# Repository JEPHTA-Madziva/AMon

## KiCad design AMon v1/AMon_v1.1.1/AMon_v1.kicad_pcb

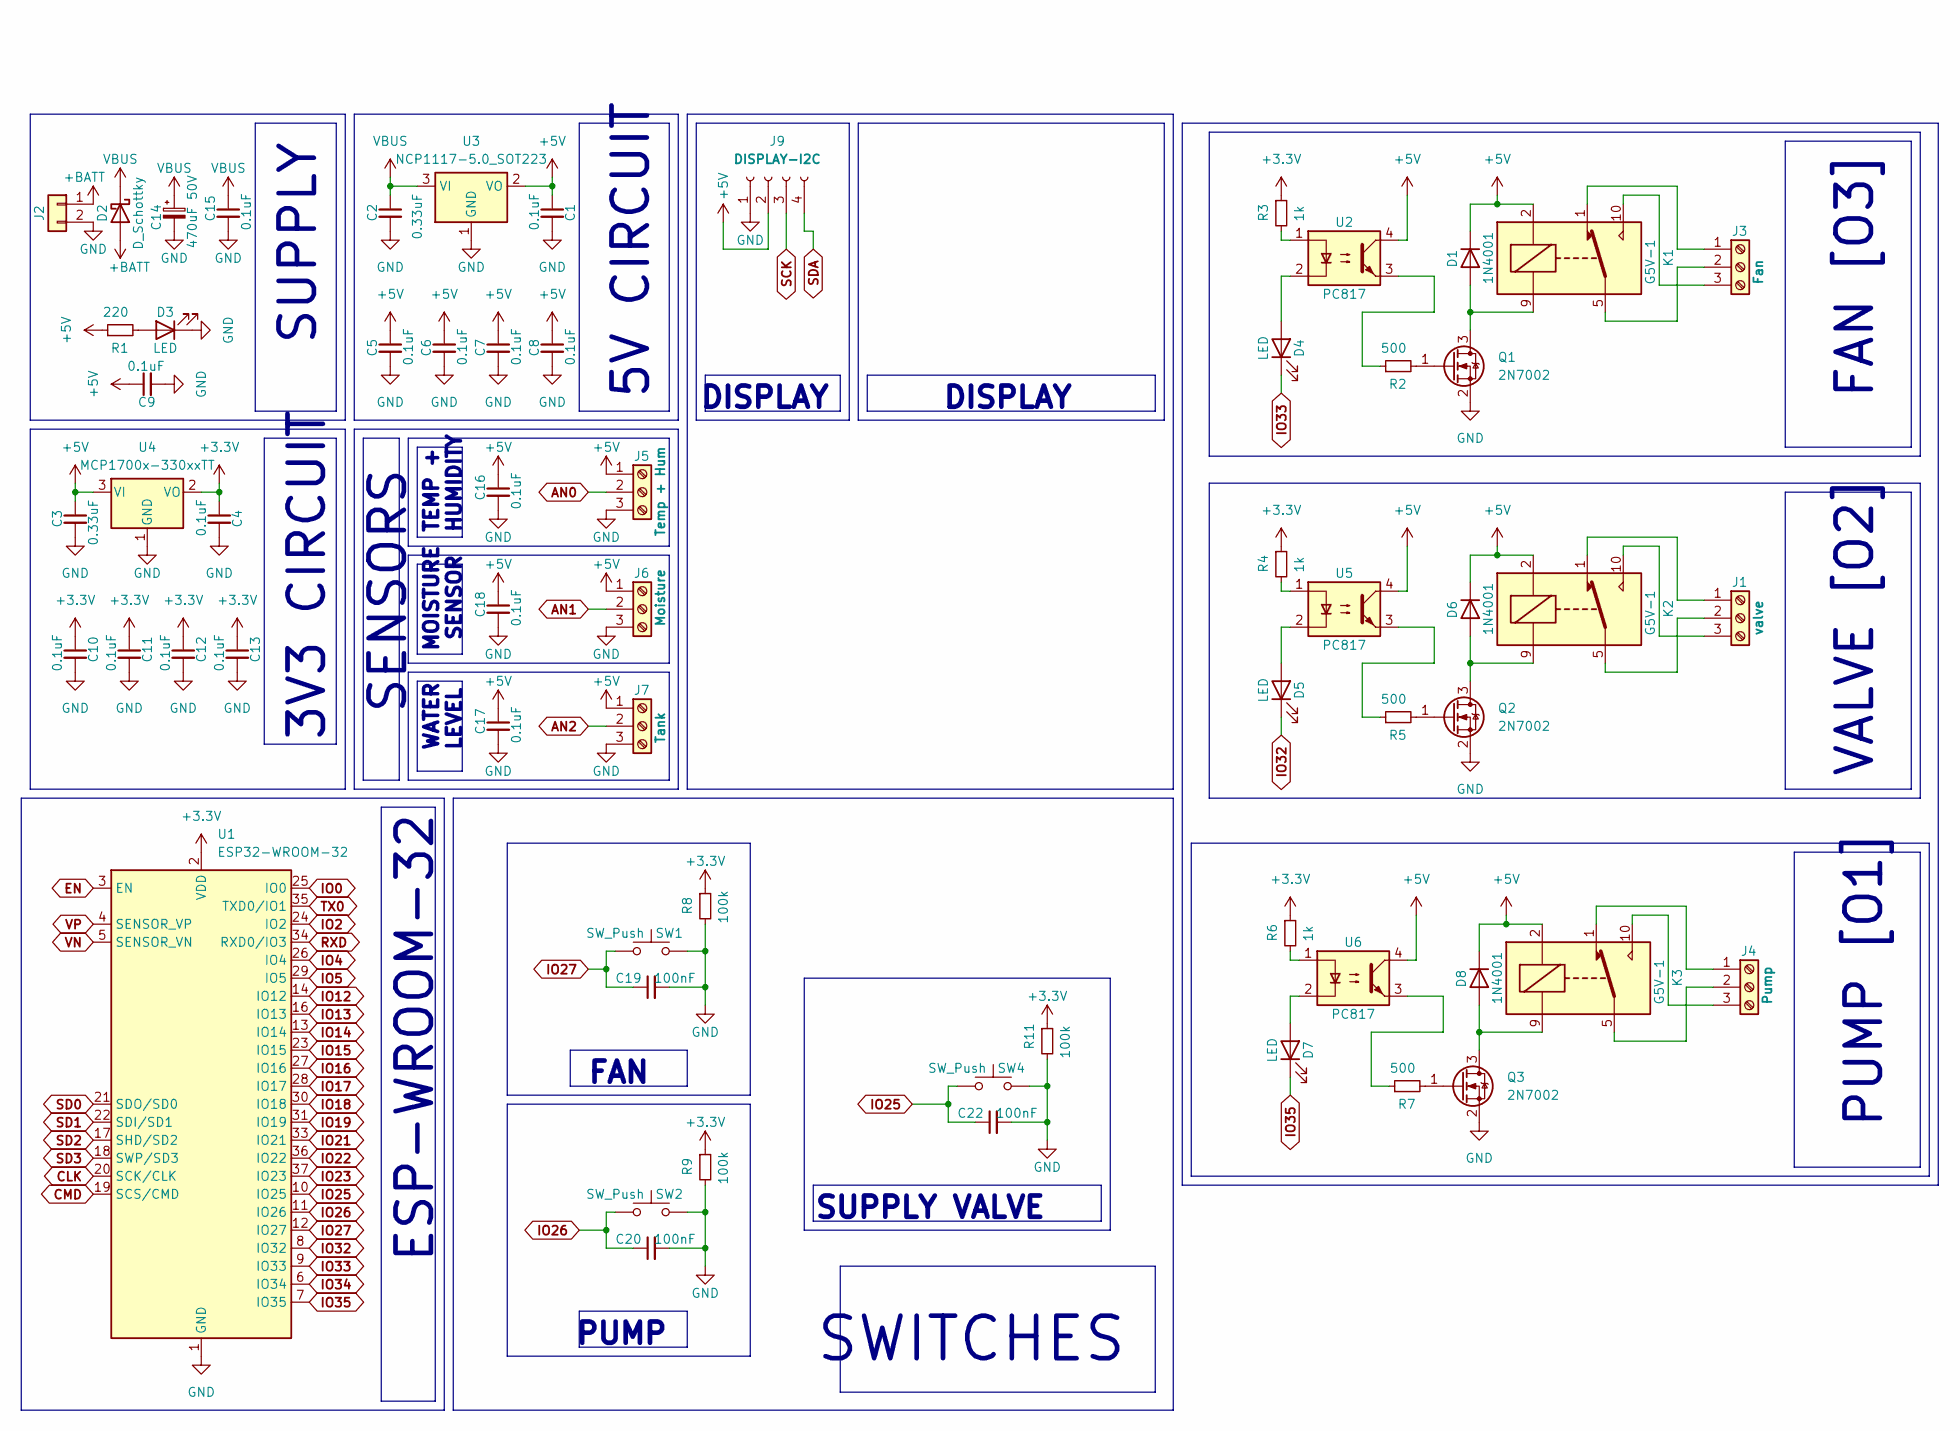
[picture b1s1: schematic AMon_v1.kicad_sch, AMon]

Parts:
C1, C4, C5, C6, C7, C8, C9, C10, C11, C12, C13, C15, C16, C17, C18: 0.1uF; C_1206_3216Metric
C2, C3: 0.33uF; C_1206_3216Metric
C14: 470uF 50V; CP_Elec_5x3.9
C19, C20, C22: 100nF; C_1206_3216Metric
D1, D6, D8: 1N4001; D_DO-41_SOD81_P10.16mm_Horizontal
D2: D_Schottky; D_DO-35_SOD27_P7.62mm_Horizontal
D3, D4, D5, D7: LED; LED_0805_2012Metric
J1: valve; TerminalBlock_Phoenix_MKDS-3-3-5.08_1x03_P5.08mm_Horizontal
J2: Conn_01x02; JST_EH_S2B-EH_1x02_P2.50mm_Horizontal
J3: Fan; TerminalBlock_Phoenix_MKDS-3-3-5.08_1x03_P5.08mm_Horizontal
J4: Pump; TerminalBlock_Phoenix_MKDS-3-3-5.08_1x03_P5.08mm_Horizontal
J5: Temp + Hum; TerminalBlock_Phoenix_MKDS-3-3-5.08_1x03_P5.08mm_Horizontal
J6: Moisture; TerminalBlock_Phoenix_MKDS-3-3-5.08_1x03_P5.08mm_Horizontal
J7: Tank; TerminalBlock_Phoenix_MKDS-3-3-5.08_1x03_P5.08mm_Horizontal
J9: DISPLAY-I2C; PinSocket_1x04_P2.54mm_Vertical
K1, K2, K3: G5V-1; Relay_SPDT_Omron_G5V-1
Q1, Q2, Q3: 2N7002; SOT-23
R1: 220; R_1206_3216Metric
R2, R5, R7: 500; R_1206_3216Metric
R3, R4, R6: 1k; R_1206_3216Metric
R8, R9, R11: 100k; R_1206_3216Metric
SW1, SW2, SW4: SW_Push; SW_SPST_B3U-1000P
U1: ESP32-WROOM-32
U2, U5, U6: PC817; DIP-4_W7.62mm
U3: NCP1117-5.0_SOT223; SOT-223-3_TabPin2
U4: MCP1700x-330xxTT; SOT-23

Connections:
+3.3V: C4.1, C10.1, C11.1, C12.1, C13.1, R3.1, R4.1, R6.1, R8.1, R9.1, R11.1, U1.2 (VDD), U4.2 (VO)
+5V: C1.1, C3.1, C5.1, C6.1, C7.1, C8.1, C9.1, C16.1, C17.1, C18.1, D1.1 (K), D6.1 (K), D8.1 (K), J5.1, J6.1, J7.1, J9.2, K1.2, K2.2, K3.2, R1.1, U2.4, U3.2 (VO), U4.3 (VI), U5.4, U6.4
+BATT: D2.2 (A), J2.1
AN0: J5.2
AN1: J6.2
AN2: J7.2
CLK: U1.20 (SCK/CLK)
CMD: U1.19 (SCS/CMD)
EN: U1.3 (EN)
GND: C1.2, C2.2, C3.2, C4.2, C5.2, C6.2, C7.2, C8.2, C9.2, C10.2, C11.2, C12.2, C13.2, C14.2, C15.2, C16.2, C17.2, C18.2, C19.2, C20.2, C22.2, D3.1 (K), J2.2, J5.3, J6.3, J7.3, J9.1, Q1.2 (S), Q2.2 (S), Q3.2 (S), R8.2, R9.2, R11.2, SW1.2, SW2.2, SW4.2, U1.1 (GND), U1.15 (GND), U1.38 (GND), U1.39 (GND), U3.1 (GND), U4.1 (GND)
IO0: U1.25 (IO0)
IO2: U1.24 (IO2)
IO4: U1.26 (IO4)
IO5: U1.29 (IO5)
IO12: U1.14 (IO12)
IO13: U1.16 (IO13)
IO14: U1.13 (IO14)
IO15: U1.23 (IO15)
IO16: U1.27 (IO16)
IO17: U1.28 (IO17)
IO18: U1.30 (IO18)
IO19: U1.31 (IO19)
IO21: U1.33 (IO21)
IO22: U1.36 (IO22)
IO23: U1.37 (IO23)
IO25: C22.1, SW4.1, U1.10 (IO25)
IO26: C20.1, SW2.1, U1.11 (IO26)
IO27: C19.1, SW1.1, U1.12 (IO27)
IO32: D5.1 (K), U1.8 (IO32)
IO33: D4.1 (K), U1.9 (IO33)
IO34: U1.6 (IO34)
IO35: D7.1 (K), U1.7 (IO35)
unnamed: D1.2 (A), K1.9, Q1.3 (D)
unnamed: D3.2 (A), R1.2
unnamed: D4.2 (A), U2.2
unnamed: D5.2 (A), U5.2
unnamed: D6.2 (A), K2.9, Q2.3 (D)
unnamed: D7.2 (A), U6.2
unnamed: D8.2 (A), K3.9, Q3.3 (D)
unnamed: J1.1, K2.1
unnamed: J1.2, K2.5, K2.6
unnamed: J1.3, K2.10
unnamed: J3.1, K1.1
unnamed: J3.2, K1.5, K1.6
unnamed: J3.3, K1.10
unnamed: J4.1, K3.1
unnamed: J4.2, K3.5, K3.6
unnamed: J4.3, K3.10
unnamed: Q1.1 (G), R2.2
unnamed: Q2.1 (G), R5.2
unnamed: Q3.1 (G), R7.2
unnamed: R2.1, U2.3
unnamed: R3.2, U2.1
unnamed: R4.2, U5.1
unnamed: R5.1, U5.3
unnamed: R6.2, U6.1
unnamed: R7.1, U6.3
RXD: U1.34 (RXD0/IO3)
SCK: J9.3
SD0: U1.21 (SDO/SD0)
SD1: U1.22 (SDI/SD1)
SD2: U1.17 (SHD/SD2)
SD3: U1.18 (SWP/SD3)
SDA: J9.4
TX0: U1.35 (TXD0/IO1)
VBUS: C2.1, C14.1, C15.1, D2.1 (K), U3.3 (VI)
VN: U1.5 (SENSOR_VN)
VP: U1.4 (SENSOR_VP)

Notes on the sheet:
TEMP + HUMIDITY
MOISTURE SENSOR
FAN
SUPPLY VALVE
ESP-WROOM-32
DISPLAY
WATER LEVEL
PUMP [O1]
VALVE [O2]
3V3 CIRCUIT
5V CIRCUIT
PUMP
FAN [O3]
SUPPLY
SENSORS
SWITCHES

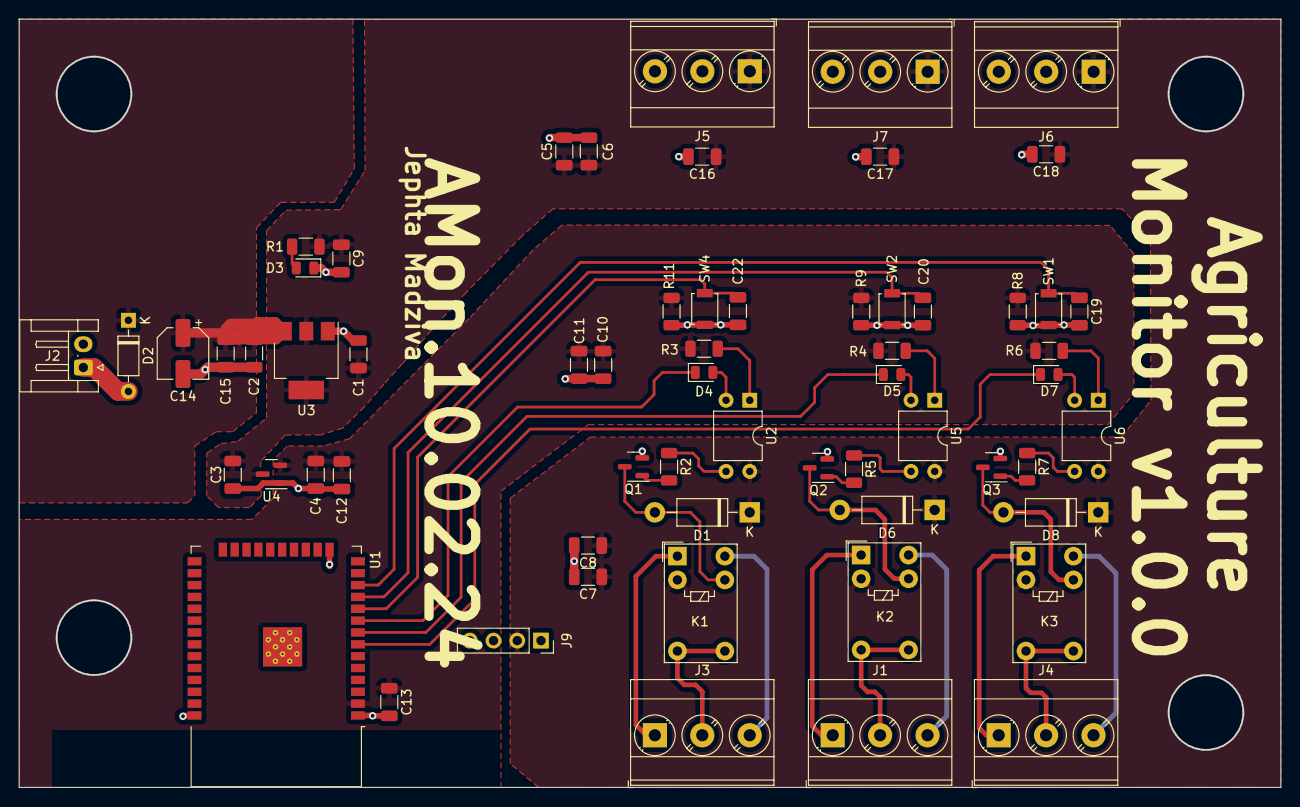
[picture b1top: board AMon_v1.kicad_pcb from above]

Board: 2 copper layers, 135.1 x 82.2 mm, 62 parts (0 on the bottom side), 36 nets.
